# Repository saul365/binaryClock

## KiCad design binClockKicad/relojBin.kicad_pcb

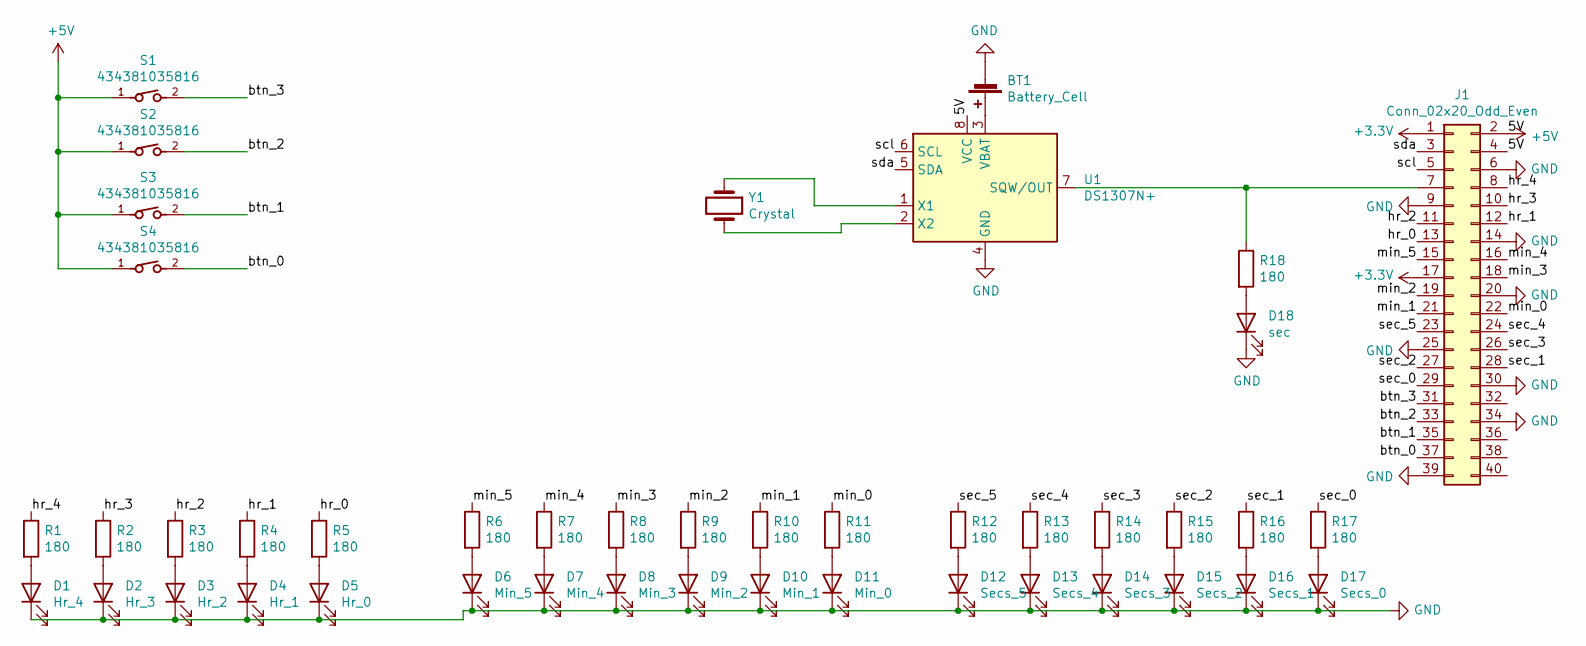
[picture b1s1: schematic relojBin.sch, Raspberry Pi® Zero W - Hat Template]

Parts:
BT1: Battery_Cell; BatteryHolder_Keystone_103_1x20mm
D1: Hr_4; LED_0603_1608Metric
D2: Hr_3; LED_0603_1608Metric
D3: Hr_2; LED_0603_1608Metric
D4: Hr_1; LED_0603_1608Metric
D5: Hr_0; LED_0603_1608Metric
D6: Min_5; LED_0603_1608Metric
D7: Min_4; LED_0603_1608Metric
D8: Min_3; LED_0603_1608Metric
D9: Min_2; LED_0603_1608Metric
D10: Min_1; LED_0603_1608Metric
D11: Min_0; LED_0603_1608Metric
D12: Secs_5; LED_0603_1608Metric
D13: Secs_4; LED_0603_1608Metric
D14: Secs_3; LED_0603_1608Metric
D15: Secs_2; LED_0603_1608Metric
D16: Secs_1; LED_0603_1608Metric
D17: Secs_0; LED_0603_1608Metric
D18: sec; LED_0603_1608Metric
J1: Conn_02x20_Odd_Even; PinHeader_2x20_P2.54mm_Vertical
R1, R2, R3, R4, R5, R6, R7, R8, R9, R10, R11, R12, R13, R14, R15, R16, R17, R18: 180; R_0603_1608Metric
S1, S2, S3, S4: 434381035816
U1: DS1307N+; DIP-8_W7.62mm
Y1: Crystal; Crystal_AT310_D3.0mm_L10.0mm_Vertical

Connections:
+3V3: J1.1, J1.17
+5V: J1.2, J1.4, S1.1, S2.1, S3.1, S4.1, U1.8 (VCC)
/btn_0: J1.37, S4.2
/btn_1: J1.35, S3.2
/btn_2: J1.33, S2.2
/btn_3: J1.31, S1.2
/hr_0: J1.13, R5.1
/hr_1: J1.12, R4.1
/hr_2: J1.11, R3.1
/hr_3: J1.10, R2.1
/hr_4: J1.8, R1.1
/min_0: J1.22, R11.1
/min_1: J1.21, R10.1
/min_2: J1.19, R9.1
/min_3: J1.18, R8.1
/min_4: J1.16, R7.1
/min_5: J1.15, R6.1
/scl: J1.5, U1.6 (SCL)
/sda: J1.3, U1.5 (SDA)
/sec_0: J1.29, R17.1
/sec_1: J1.28, R16.1
/sec_2: J1.27, R15.1
/sec_3: J1.26, R14.1
/sec_4: J1.24, R13.1
/sec_5: J1.23, R12.1
GND: BT1.2 (-), D1.1 (K), D2.1 (K), D3.1 (K), D4.1 (K), D5.1 (K), D6.1 (K), D7.1 (K), D8.1 (K), D9.1 (K), D10.1 (K), D11.1 (K), D12.1 (K), D13.1 (K), D14.1 (K), D15.1 (K), D16.1 (K), D17.1 (K), D18.1 (K), J1.6, J1.9, J1.14, J1.20, J1.25, J1.30, J1.34, J1.39, U1.4 (GND)
unnamed: BT1.1 (+), U1.3 (VBAT)
unnamed: D1.2 (A), R1.2
unnamed: D2.2 (A), R2.2
unnamed: D3.2 (A), R3.2
unnamed: D4.2 (A), R4.2
unnamed: D5.2 (A), R5.2
unnamed: D6.2 (A), R6.2
unnamed: D7.2 (A), R7.2
unnamed: D8.2 (A), R8.2
unnamed: D9.2 (A), R9.2
unnamed: D10.2 (A), R10.2
unnamed: D11.2 (A), R11.2
unnamed: D12.2 (A), R12.2
unnamed: D13.2 (A), R13.2
unnamed: D14.2 (A), R14.2
unnamed: D15.2 (A), R15.2
unnamed: D16.2 (A), R16.2
unnamed: D17.2 (A), R17.2
unnamed: D18.2 (A), R18.2
unnamed: J1.7, R18.1, U1.7 (SQW/OUT)
unnamed: U1.1 (X1), Y1.1
unnamed: U1.2 (X2), Y1.2

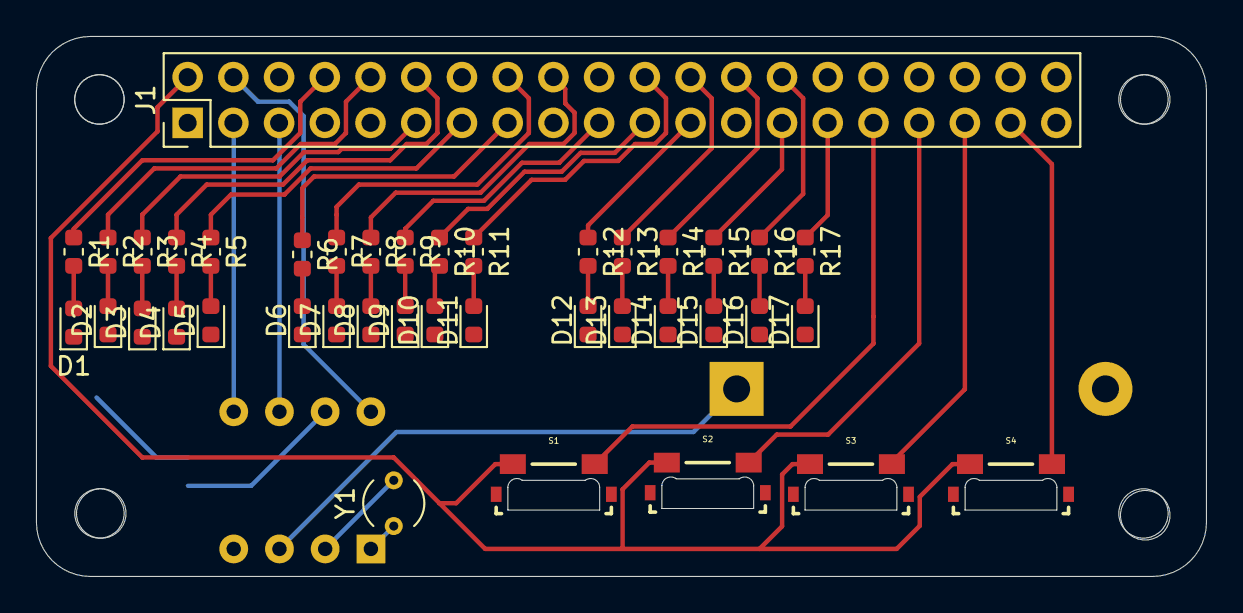
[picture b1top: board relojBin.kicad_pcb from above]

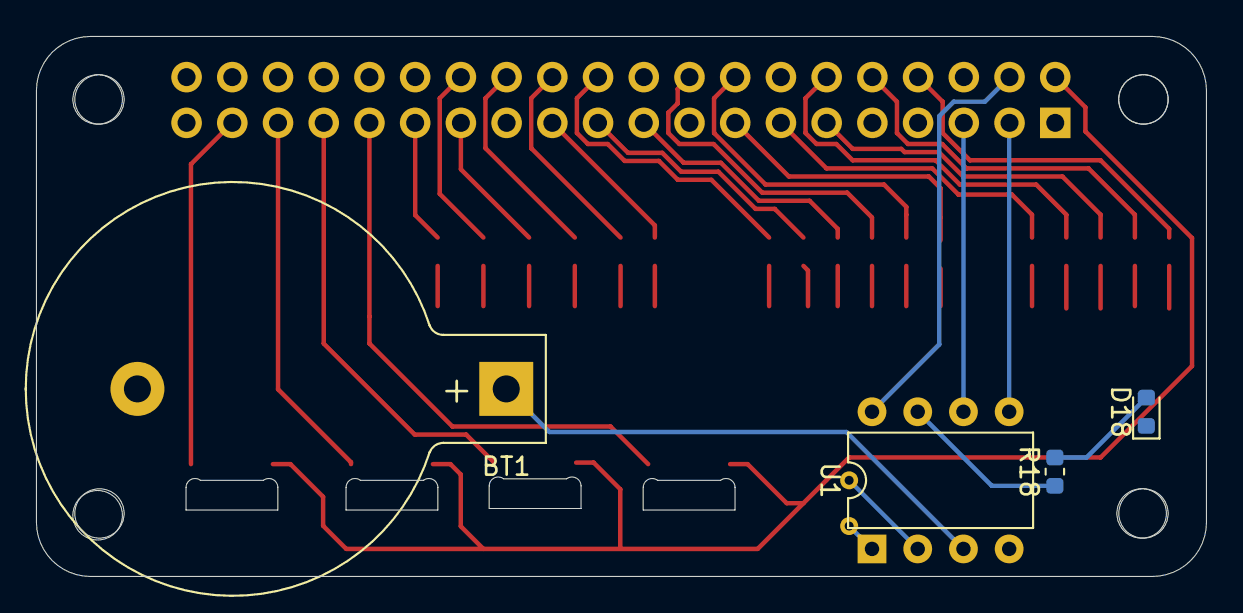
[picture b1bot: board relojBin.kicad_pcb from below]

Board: 2 copper layers, 65.0 x 30.0 mm, 44 parts (4 on the bottom side), 48 nets.

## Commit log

2019-08-26 added previous work
2019-09-04 added documentation and made it a little more universal
2019-09-14 added reader and writer i2c
2019-09-15 i2c fuly functional
2019-09-15 all done
2019-10-02 added git ignore and removed html and latex
2019-10-02 minor changes
2019-10-26 Started python Branch
2020-08-01 Add Kicad files for PiHat

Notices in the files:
binClockKicad/relojBin.kicad_pcb:
License: MIT - Copyright 2018 StudioPieters®
